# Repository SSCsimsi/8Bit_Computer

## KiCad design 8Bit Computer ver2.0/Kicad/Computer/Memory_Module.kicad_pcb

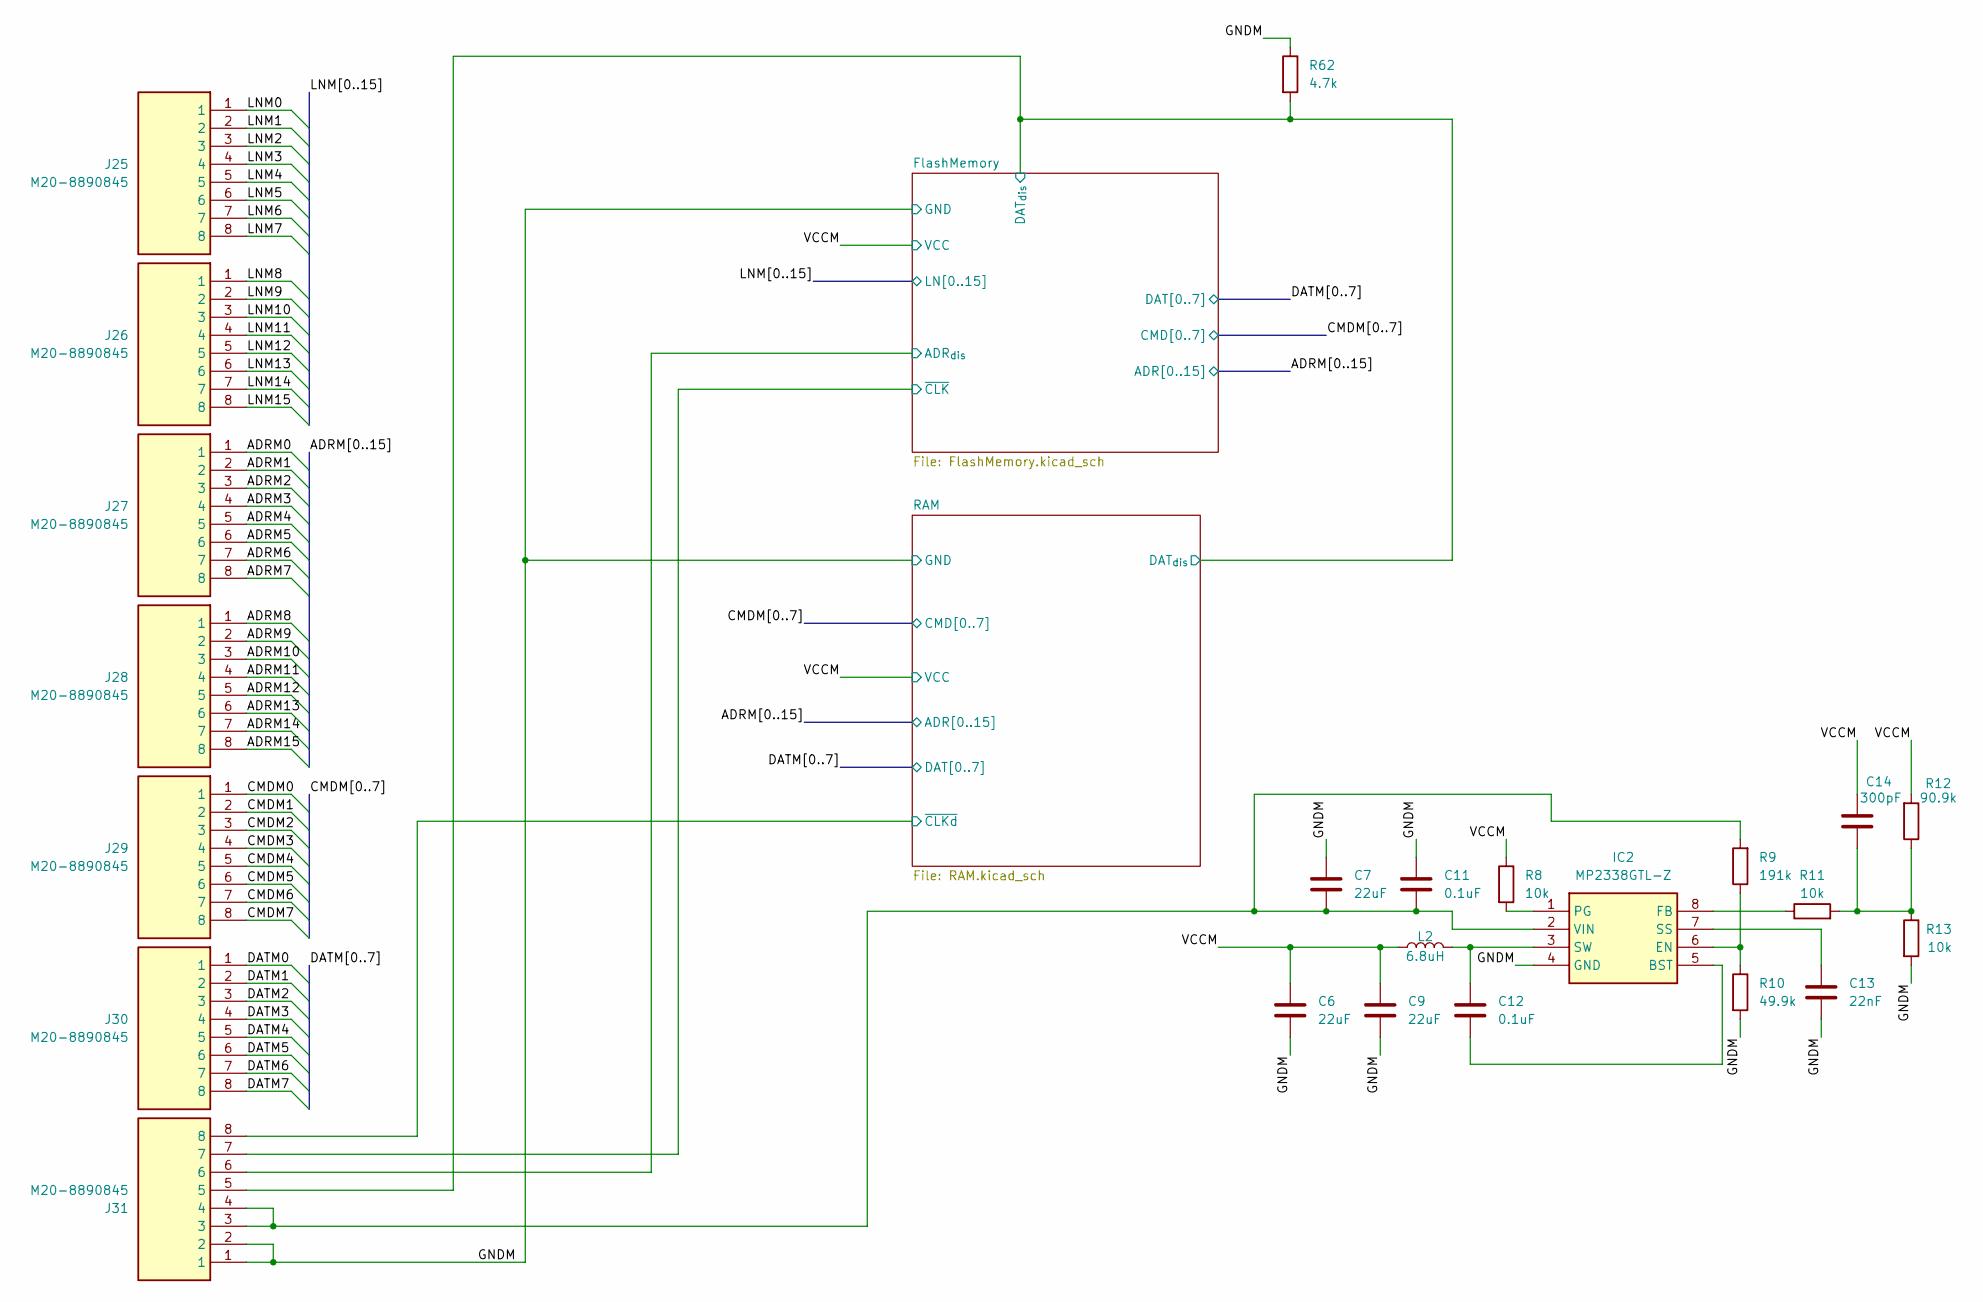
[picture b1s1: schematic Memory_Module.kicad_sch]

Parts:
C6, C7, C9: 22uF; C_1206_3216Metric_Pad1.33x1.80mm_HandSolder
C11, C12: 0.1uF; C_1206_3216Metric_Pad1.33x1.80mm_HandSolder
C13: 22nF; C_1206_3216Metric_Pad1.33x1.80mm_HandSolder
C14: 300pF; C_1206_3216Metric_Pad1.33x1.80mm_HandSolder
IC2: MP2338GTL-Z; MP2338GTLZ; Mouser Part Number 946-MP2338GTL-Z
J25, J26, J27, J28, J29, J30, J31: M20-8890845; M208890845; Mouser Part Number 855-M20-8890845
L2: 6.8uH; INDPM108100X400N; Mouser Part Number 80-MPEV1D1040L6R8
R8, R11, R13: 10k; R_1206_3216Metric_Pad1.30x1.75mm_HandSolder
R9: 191k; R_1206_3216Metric_Pad1.30x1.75mm_HandSolder
R10: 49.9k; R_1206_3216Metric_Pad1.30x1.75mm_HandSolder
R12: 90.9k; R_1206_3216Metric_Pad1.30x1.75mm_HandSolder
R62: 4.7k; R_1206_3216Metric_Pad1.30x1.75mm_HandSolder

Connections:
/ADRM0: J27.1; also elsewhere on the board
/ADRM1: J27.2; also elsewhere on the board
/ADRM2: J27.3; also elsewhere on the board
/ADRM3: J27.4; also elsewhere on the board
/ADRM4: J27.5; also elsewhere on the board
/ADRM5: J27.6; also elsewhere on the board
/ADRM6: J27.7; also elsewhere on the board
/ADRM7: J27.8; also elsewhere on the board
/ADRM8: J28.1; also elsewhere on the board
/ADRM9: J28.2; also elsewhere on the board
/ADRM10: J28.3; also elsewhere on the board
/ADRM11: J28.4; also elsewhere on the board
/ADRM12: J28.5; also elsewhere on the board
/ADRM13: J28.6; also elsewhere on the board
/ADRM14: J28.7; also elsewhere on the board
/ADRM15: J28.8; also elsewhere on the board
/CMDM0: J29.1; also elsewhere on the board
/CMDM1: J29.2; also elsewhere on the board
/CMDM2: J29.3; also elsewhere on the board
/CMDM3: J29.4; also elsewhere on the board
/CMDM4: J29.5; also elsewhere on the board
/CMDM5: J29.6; also elsewhere on the board
/CMDM6: J29.7; also elsewhere on the board
/CMDM7: J29.8; also elsewhere on the board
/DATM0: J30.1; also elsewhere on the board
/DATM1: J30.2; also elsewhere on the board
/DATM2: J30.3; also elsewhere on the board
/DATM3: J30.4; also elsewhere on the board
/DATM4: J30.5; also elsewhere on the board
/DATM5: J30.6; also elsewhere on the board
/DATM6: J30.7; also elsewhere on the board
/DATM7: J30.8; also elsewhere on the board
/FlashMemory/ADR_{dis}: J31.6; also elsewhere on the board
/FlashMemory/DAT_{dis}: J31.5, R62.2; also elsewhere on the board
/FlashMemory/~CLK: J31.7; also elsewhere on the board
/GNDM: C6.2, C7.1, C9.2, C11.1, C13.2, IC2.4 (GND), J31.1, J31.2, R10.2, R13.2, R62.1; also elsewhere on the board
/LNM0: J25.1; also elsewhere on the board
/LNM1: J25.2; also elsewhere on the board
/LNM2: J25.3; also elsewhere on the board
/LNM3: J25.4; also elsewhere on the board
/LNM4: J25.5; also elsewhere on the board
/LNM5: J25.6; also elsewhere on the board
/LNM6: J25.7; also elsewhere on the board
/LNM7: J25.8; also elsewhere on the board
/LNM8: J26.1; also elsewhere on the board
/LNM9: J26.2; also elsewhere on the board
/LNM10: J26.3; also elsewhere on the board
/LNM11: J26.4; also elsewhere on the board
/LNM12: J26.5; also elsewhere on the board
/LNM13: J26.6; also elsewhere on the board
/LNM14: J26.7; also elsewhere on the board
/LNM15: J26.8; also elsewhere on the board
/RAM/~CLKd: J31.8; also elsewhere on the board
/VCCM: C6.1, C9.1, C14.1, L2.1, R8.1, R12.2; also elsewhere on the board
unnamed: C14.2, R11.2, R12.1, R13.1
unnamed: C12.2, IC2.5 (BST)
unnamed: IC2.6 (EN), R9.1, R10.1
unnamed: IC2.8 (FB), R11.1
unnamed: IC2.1 (PG), R8.2
unnamed: C13.1, IC2.7 (SS)
unnamed: C12.1, IC2.3 (SW), L2.2
unnamed: C7.2, C11.2, IC2.2 (VIN), J31.3, J31.4, R9.2

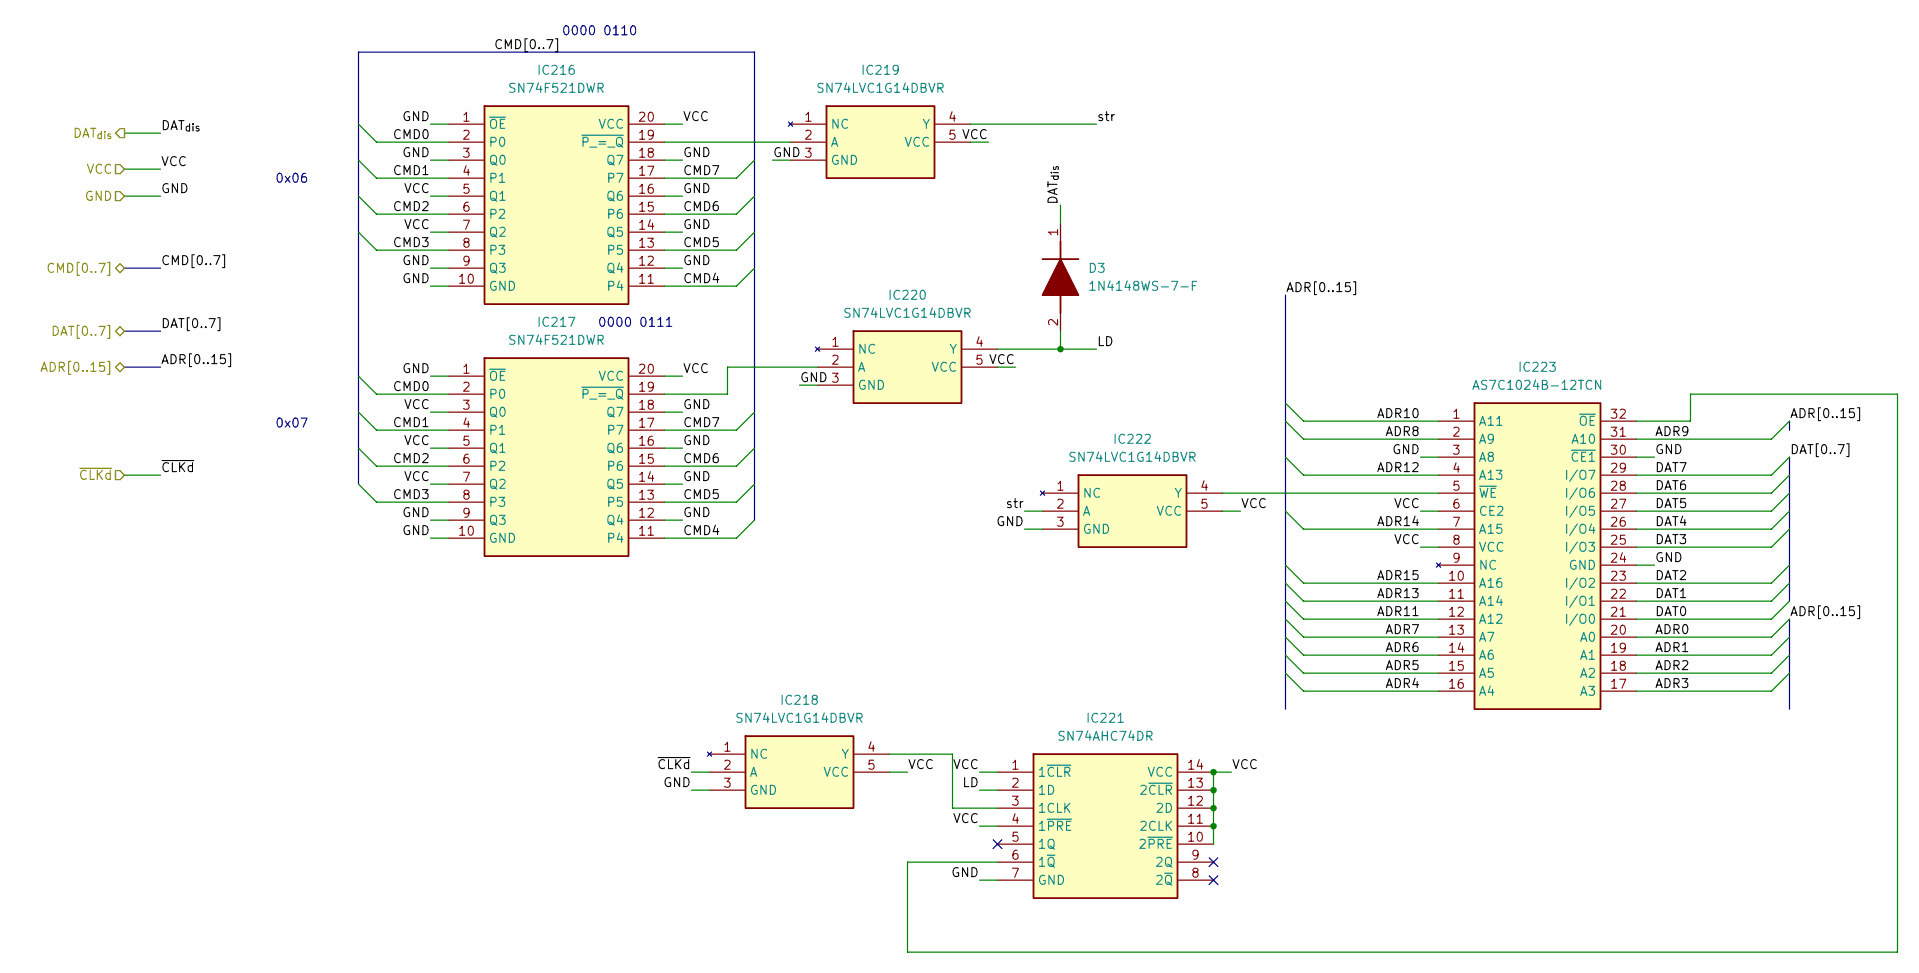
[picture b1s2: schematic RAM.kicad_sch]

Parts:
D3: 1N4148WS-7-F; SOD2513X120N; Mouser Part Number 621-1N4148WS-F
IC216, IC217: SN74F521DWR; SOIC127P1030X265-20N; Mouser Part Number 595-SN74F521DWR
IC218, IC219, IC220, IC222: SN74LVC1G14DBVR; SOT95P280X145-5N; Mouser Part Number 595-SN74LVC1G14DBVR
IC221: SN74AHC74DR; SOIC127P600X175-14N; Mouser Part Number 595-SN74AHC74DR
IC223: AS7C1024B-12TCN; SOP50P2000X120-32N; Mouser Part Number 913-AS7C1024B-12TCN

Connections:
/ADRM0: IC223.20 (A0); also elsewhere on the board
/ADRM1: IC223.19 (A1); also elsewhere on the board
/ADRM2: IC223.18 (A2); also elsewhere on the board
/ADRM3: IC223.17 (A3); also elsewhere on the board
/ADRM4: IC223.16 (A4); also elsewhere on the board
/ADRM5: IC223.15 (A5); also elsewhere on the board
/ADRM6: IC223.14 (A6); also elsewhere on the board
/ADRM7: IC223.13 (A7); also elsewhere on the board
/ADRM8: IC223.2 (A9); also elsewhere on the board
/ADRM9: IC223.31 (A10); also elsewhere on the board
/ADRM10: IC223.1 (A11); also elsewhere on the board
/ADRM11: IC223.12 (A12); also elsewhere on the board
/ADRM12: IC223.4 (A13); also elsewhere on the board
/ADRM13: IC223.11 (A14); also elsewhere on the board
/ADRM14: IC223.7 (A15); also elsewhere on the board
/ADRM15: IC223.10 (A16); also elsewhere on the board
/CMDM0: IC216.2 (P0), IC217.2 (P0); also elsewhere on the board
/CMDM1: IC216.4 (P1), IC217.4 (P1); also elsewhere on the board
/CMDM2: IC216.6 (P2), IC217.6 (P2); also elsewhere on the board
/CMDM3: IC216.8 (P3), IC217.8 (P3); also elsewhere on the board
/CMDM4: IC216.11 (P4), IC217.11 (P4); also elsewhere on the board
/CMDM5: IC216.13 (P5), IC217.13 (P5); also elsewhere on the board
/CMDM6: IC216.15 (P6), IC217.15 (P6); also elsewhere on the board
/CMDM7: IC216.17 (P7), IC217.17 (P7); also elsewhere on the board
/DATM0: IC223.21 (I/O0); also elsewhere on the board
/DATM1: IC223.22 (I/O1); also elsewhere on the board
/DATM2: IC223.23 (I/O2); also elsewhere on the board
/DATM3: IC223.25 (I/O3); also elsewhere on the board
/DATM4: IC223.26 (I/O4); also elsewhere on the board
/DATM5: IC223.27 (I/O5); also elsewhere on the board
/DATM6: IC223.28 (I/O6); also elsewhere on the board
/DATM7: IC223.29 (I/O7); also elsewhere on the board
/GNDM: IC216.1 (~OE), IC216.3 (Q0), IC216.9 (Q3), IC216.10 (GND), IC216.12 (Q4), IC216.14 (Q5), IC216.16 (Q6), IC216.18 (Q7), IC217.1 (~OE), IC217.9 (Q3), IC217.10 (GND), IC217.12 (Q4), IC217.14 (Q5), IC217.16 (Q6), IC217.18 (Q7), IC218.3 (GND), IC219.3 (GND), IC220.3 (GND), IC221.7 (GND), IC222.3 (GND), IC223.3 (A8), IC223.24 (GND), IC223.30 (~CE1); also elsewhere on the board
/RAM/DAT_{dis}: D3.1 (K); also elsewhere on the board
/RAM/LD: D3.2 (A), IC220.4 (Y), IC221.2 (1D)
/RAM/str: IC219.4 (Y), IC222.2 (A)
/RAM/~CLKd: IC218.2 (A); also elsewhere on the board
/VCCM: IC216.5 (Q1), IC216.7 (Q2), IC216.20 (VCC), IC217.3 (Q0), IC217.5 (Q1), IC217.7 (Q2), IC217.20 (VCC), IC218.5 (VCC), IC219.5 (VCC), IC220.5 (VCC), IC221.1 (1~CLR), IC221.4 (1~PRE), IC221.10 (2~PRE), IC221.11 (2CLK), IC221.12 (2D), IC221.13 (2~CLR), IC221.14 (VCC), IC222.5 (VCC), IC223.6 (CE2), IC223.8 (VCC); also elsewhere on the board
unnamed: IC216.19 (~P_=_Q), IC219.2 (A)
unnamed: IC217.19 (~P_=_Q), IC220.2 (A)
unnamed: IC218.4 (Y), IC221.3 (1CLK)
unnamed: IC221.6 (1~Q), IC223.32 (~OE)
unnamed: IC222.4 (Y), IC223.5 (~WE)

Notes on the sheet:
0x07
0x06
0000 0111
0000 0110
